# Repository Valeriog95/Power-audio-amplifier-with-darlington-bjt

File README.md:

# Power-audio-amplifier-with-darlington-bjt

Hello everyone,
This repository shows a base amplifier made with only discrete components (without op-amp), it provides 25 watt  @ 8ohm.

I completed this project at 18 for my high school exam at ITIS Enrico Fermi institute in Rome and have made no changes since (relation remained in its original language). Later on, i created the board (using KiCad 5.0) and tested it using an electronic load and a signal generator/analyzer keithley2015.

Some features:

- More than 60% efficiency;
- THD less than 0.03% @ 1 watt;
- S/N > 85dB;

I'm open to any critiques/suggestions.

Hope that this simple project is helpful!

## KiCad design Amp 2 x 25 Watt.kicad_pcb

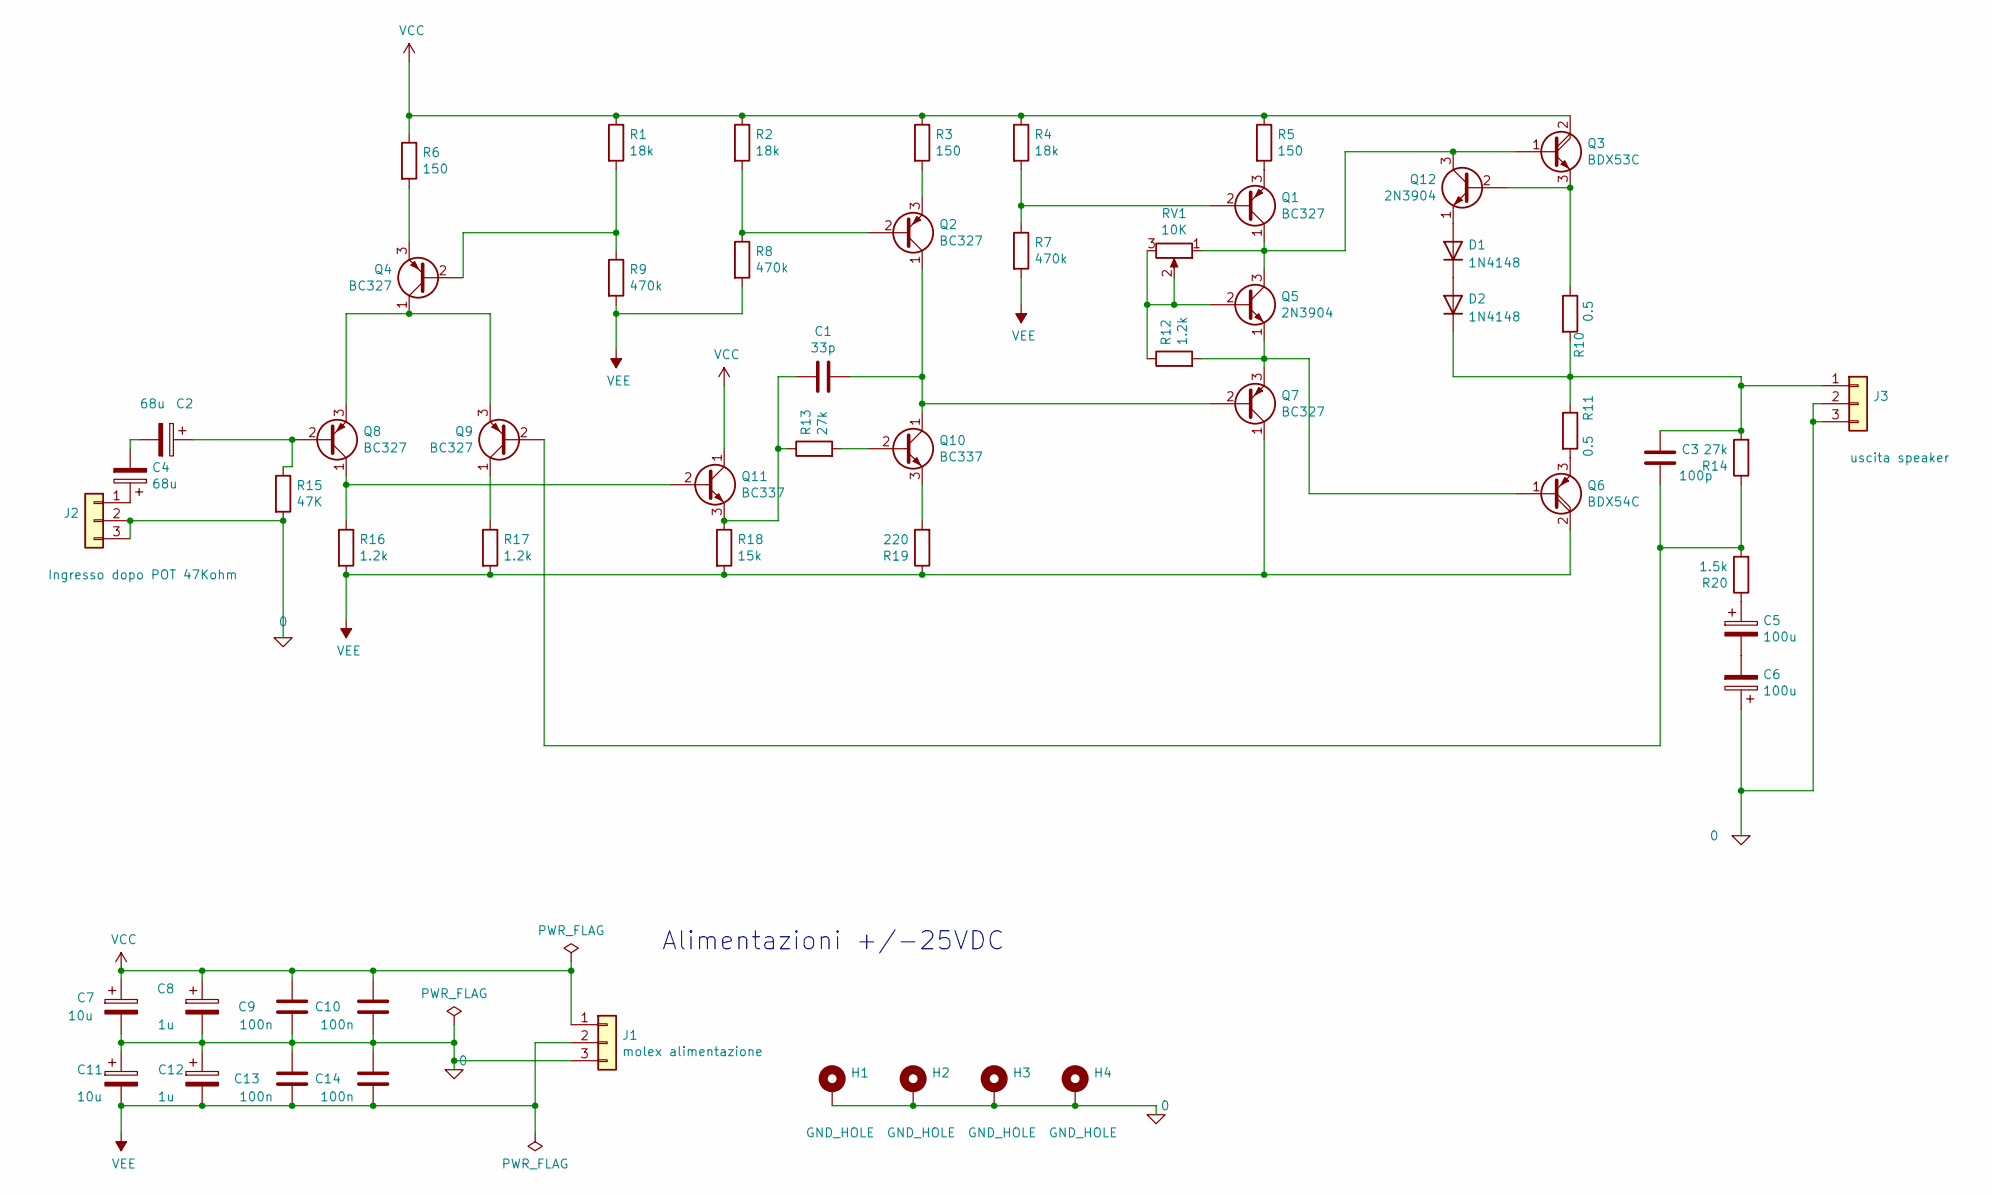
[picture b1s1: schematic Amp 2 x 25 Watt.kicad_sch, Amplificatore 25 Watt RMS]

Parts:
C1: 33p; C_Disc_D7.0mm_W2.5mm_P5.00mm
C2, C4: 68u; CP_Radial_D6.3mm_P2.50mm
C3: 100p; C_Disc_D7.0mm_W2.5mm_P5.00mm
C5, C6: 100u; CP_Radial_D8.0mm_P3.50mm
C7, C11: 10u; CP_Radial_D5.0mm_P2.00mm
C8, C12: 1u; CP_Radial_D5.0mm_P2.50mm
C9, C10, C13, C14: 100n; C_Rect_L7.2mm_W5.5mm_P5.00mm_FKS2_FKP2_MKS2_MKP2
D1, D2: 1N4148; D_DO-35_SOD27_P7.62mm_Horizontal
H1, H2, H3, H4: GND_HOLE; MountingHole_3.2mm_M3_DIN965_Pad_TopBottom
J1: molex alimentazione; Connectors_threeway
J2: Ingresso dopo POT 47Kohm; Connectors_threeway
J3: uscita speaker; Connectors_threeway
Q1, Q2, Q4, Q7, Q8, Q9: BC327; TO-92_Inline
Q3: BDX53C; TO-220-3_Vertical
Q5, Q12: 2N3904; TO-92_Inline
Q6: BDX54C; TO-220-3_Vertical
Q10, Q11: BC337; TO-92_Inline
R1, R2, R4: 18k; R_Axial_DIN0207_L6.3mm_D2.5mm_P10.16mm_Horizontal
R3, R5, R6: 150; R_Axial_DIN0207_L6.3mm_D2.5mm_P10.16mm_Horizontal
R7, R8, R9: 470k; R_Axial_DIN0207_L6.3mm_D2.5mm_P10.16mm_Horizontal
R10, R11: 0.5; R_Axial_Power_L25.0mm_W6.4mm_P27.94mm
R12, R16, R17: 1.2k; R_Axial_DIN0207_L6.3mm_D2.5mm_P10.16mm_Horizontal
R13, R14: 27k; R_Axial_DIN0207_L6.3mm_D2.5mm_P10.16mm_Horizontal
R15: 47K; R_Axial_DIN0207_L6.3mm_D2.5mm_P10.16mm_Horizontal
R18: 15k; R_Axial_DIN0207_L6.3mm_D2.5mm_P10.16mm_Horizontal
R19: 220; R_Axial_DIN0207_L6.3mm_D2.5mm_P10.16mm_Horizontal
R20: 1.5k; R_Axial_DIN0207_L6.3mm_D2.5mm_P10.16mm_Horizontal
RV1: 10K; Potentiometer_ACP_CA9-V10_Vertical

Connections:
0: C6.1, C7.2, C8.2, C9.2, C10.2, C11.1, C12.1, C13.1, C14.1, H1.1, H2.1, H3.1, H4.1, J1.3, J2.2, J2.3, J3.2, J3.3, R15.2
unnamed: C1.1, Q2.1 (C), Q7.2 (B), Q10.1 (C)
unnamed: C1.2, Q11.3 (E), R13.1, R18.1
unnamed: C2.1, Q8.2 (B), R15.1
unnamed: C2.2, C4.2
unnamed: C3.1, D2.1 (K), J3.1, R10.2, R11.1, R14.2
unnamed: C3.2, Q9.2 (B), R14.1, R20.2
unnamed: C4.1, J2.1
unnamed: C5.1, R20.1
unnamed: C5.2, C6.2
unnamed: D1.1 (K), D2.2 (A)
unnamed: D1.2 (A), Q12.1 (E)
unnamed: Q1.1 (C), Q3.1 (B), Q5.3 (C), Q12.3 (C), RV1.1
unnamed: Q1.2 (B), R4.2, R7.1
unnamed: Q1.3 (E), R5.2
unnamed: Q2.2 (B), R2.2, R8.1
unnamed: Q2.3 (E), R3.2
unnamed: Q4.1 (C), Q8.3 (E), Q9.3 (E)
unnamed: Q4.2 (B), R1.2, R9.1
unnamed: Q4.3 (E), R6.2
unnamed: Q5.1 (E), Q6.1 (B), Q7.3 (E), R12.2
unnamed: Q5.2 (B), R12.1, RV1.2, RV1.3
unnamed: Q6.3 (E), R11.2
unnamed: Q9.1 (C), R17.1
unnamed: Q10.2 (B), R13.2
unnamed: Q10.3 (E), R19.2
unnamed: Q8.1 (C), Q11.2 (B), R16.1
unnamed: Q3.3 (E), Q12.2 (B), R10.1
VCC: C7.1, C8.1, C9.1, C10.1, J1.1, Q3.2 (C), Q11.1 (C), R1.1, R2.1, R3.1, R4.1, R5.1, R6.1
VEE: C11.2, C12.2, C13.2, C14.2, J1.2, Q6.2 (C), Q7.1 (C), R7.2, R8.2, R9.2, R16.2, R17.2, R18.2, R19.1

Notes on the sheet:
Alimentazioni +/-25VDC

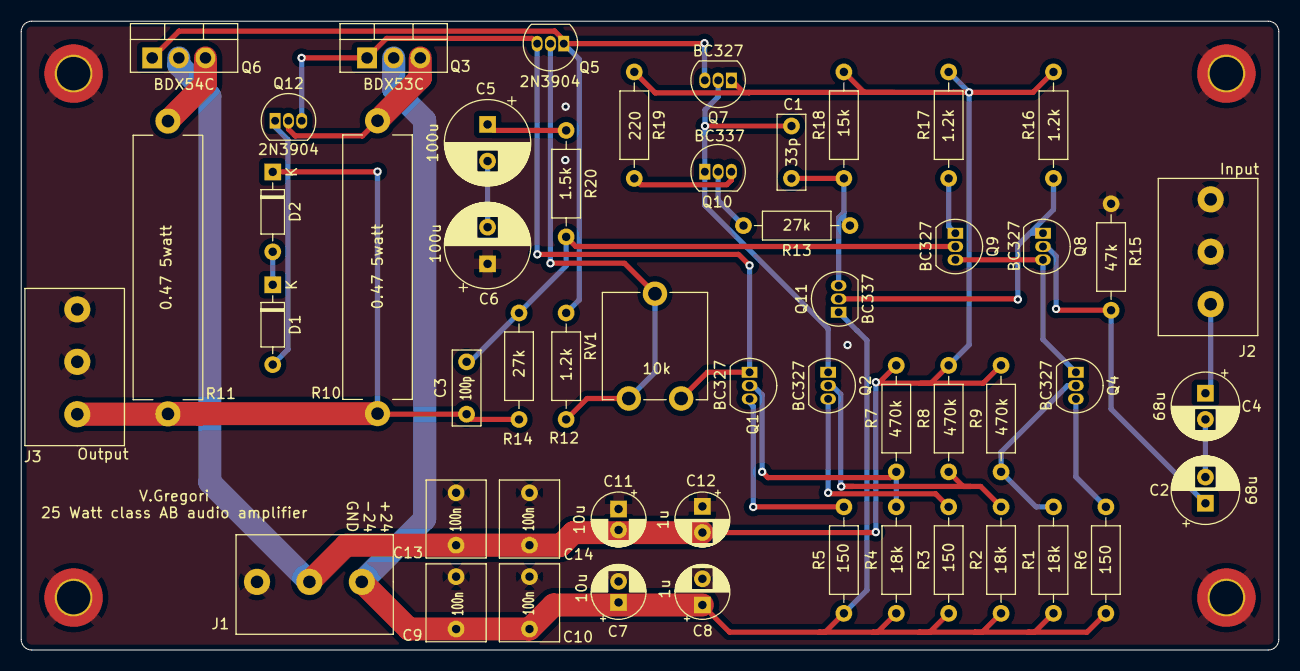
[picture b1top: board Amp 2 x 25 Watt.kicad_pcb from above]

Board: 2 copper layers, 120.0 x 60.0 mm, 56 parts (0 on the bottom side), 30 nets.

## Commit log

2023-04-17 Kicad PRJ
    Schematic and board Layout
